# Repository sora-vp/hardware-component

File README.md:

<p align="center">
   
   <h1 align="center">SORA BUTTON MODULE</h1>
</p>

Ini adalah repositori pendukung [sora](https://github.com/reacto11mecha/sora) membuat tombol custom untuk memilih kandidat. Harapannya jika tidak ada perangkat touchscreen dan ada orang yang tidak bisa mengoperasikan komputer dengan baik masih bisa ikut memilih seperti biasanya.

## Cara pembuatan tombol custom

Di bawah ini saya akan menjelaskan bagaimana cara membuat modul tombol mandiri. Jika ada hal yang ingin dirubah, silahkan ubah sesuka hati sesuai bahan dan kreativitas masing-masing.

## Siapkan alat bahan

Pertama, siapkan terlebih dahulu alat dan bahan seperti

1. Gunting / cutter
2. Arduino Nano v3.0
3. Kardus bekas
4. Solder
5. Timah
6. Kabel (5 Meter, minimal 16 AWG)
7. Push button (8 buah)
8. Lem tembak beserta isinya.
9. PCB bolong (8x16cm)

> Catatan, untuk kardus dan arduino bisa menyesuaikan budget yang ada. Untuk tutorial di readme ini akan menggunakan kardus sebagai boxnya.

### 1. Buat kerangka

Hasil percobaan yang saya lakukan menghasilkan ukuran kerangka dengan bentuk jaring-jaring balok yang terlihat seperti ini.

Balok ini memiliki panjang 21 cm, lebar 15 cm, dan tinggi 7 cm.

### 2. Potong setiap bagian sebanyak dua lembar

Jika kerangka sudah dibuat, potong setiap bagian menjadi dua lembar kardus. Kemudian rekatkan menggunakan lem tembak supaya kekuatan kardus tidak terlalu lemah.

### 3. Mengatur jarak antar tombol

Untuk penempatan tombol, gunakan jaring-jaring balok dari kardus yang sudah dibuat menggunakan bagian tutup balok.

Panjang keseluruhan peletakan tombol itu 15cm untuk tombol kandidat dan aksi pilih dan pembatalan.

Untuk tombol angka yang nantinya digunakan untuk memilih kandidat, beri jarak 5cm dari atas juga 3 cm dari kanan dan kiri. Jarak antar tombol memiliki panjang 3.7cm supaya sesuai.

Tombol batal dan pilih juga beri jarak dari bawah. Tombol batal mengikuti posisi tombol nomor 1, sedangkan tombol pilih mengikuti posisi tombol nomor 5.

Tombol reload diposisikan sejajar dengan tombol nomor 5, posisi berjarak 3 cm dari kiri, 3.5 cm dari atas.

Jika sudah pasang lubangi titik-titik yang sudah dibuat, lalu pasang tombol yang sebelumnya sudah disiapkan. Kurang lebih hasilnya akan seperti ini.

> Jika memperhatikan gambar di atas ada 4 lubang di dua sisi kanan dan kiri kardus, itu berfungsi sebagai lubang udara. Ini opsional tetapi

### 4. Merancang sirkuit

Desain tombol ini sangat berdasar pada artikel [makeuseof.com](https://www.makeuseof.com/tag/make-custom-shortcut-buttons-arduino/) yang membahas cara membuat tombol sendiri. Kurang lebih gambar sirkuitnya sama, yang membedakan saya hanya menggunakan D2 sampai D9 saja.

Gambar di atas merupakan gambaran dasar sirkuitnya. Jika diperhatikan pin D2 sampai D9 menggunakan transistor 10k ohm yang warna emas terhubung ke pin arduino, sedangkan seluruh resisto warna coklat akan tersambung ke pin ground atau `GND`.

Gambar di atas adalah versi yang nantinya akan digunakan.

### 5. Menambahkan kabel ke tombol dan lem tombol

Jika sudah merancang sirkuitnya, sekarang sambungkan kabel ke tombol dengan cara menyolder kabel supaya sambungannya kuat. Berlaku untuk semua tombol, kira-kira tampaknya akan terlihat seperti dua gambar dibawah ini.

Jika sudah, lem semua tombol supaya tidak mudah lepas dari kardus. Hal ini juga dapat mengurangi kerusakan jika tombol ditekan terlalu keras.

### 6. Menyambungkan kabel ke sirkuit

Jika sudah menambahkan kabel ke tombol-tombol yang ada, saatnya menyambungkan tombol ke sirkuit yang sudah dibuat sebelumnya. `5V` terhubung ke satu sisi dari tombol, sisi yang lain akan terhubung ke digital pin dari arduino.

Jika berpatokan pada kode di bawah ini,

```ino
const int ESC_PIN = 4;
const int KEYBIND_1_PIN = 9;
const int KEYBIND_2_PIN = 8;
const int KEYBIND_3_PIN = 7;
const int KEYBIND_4_PIN = 6;
const int KEYBIND_5_PIN = 5;
const int ENTER_PIN = 3;
const int RELOAD_PIN = 2;
```

Maka

- Tombol 1 => Pin D9
- Tombol 2 => Pin D8
- Tombol 3 => Pin D7
- Tombol 4 => Pin D6
- Tombol 5 => Pin D5
- Tombol Escape (Kiri Bawah) => Pin D4
- Tombol Enter (Kanan Bawah) => Pin D3
- Tombol Reload (Sisi depan, bersamaan port usb) => Pin D2

Gambar setelah di sambungkan menggunakan solder akan terlihat seperti ini.

> Sekali lagi, sesuaikan dengan kebutuhan

### 7. Memposisikan sirkuit dengan papan reload

Pada tahap ini, posisikan pcb dengan arduino yang sudah di rekatkan dengan kardus yang memiliki tombol reload. Disarkankan posisi yang bisa dipasang port mini usb ke arduino berada berseberangan dengan tombol reload. Jika sudah, buat lubang kotak untuk tempat terhubungnya arduino melalui USB.

Tampak depan setelah dilubangi.

### 8. Lem semua komponen

Jika dirasa sudah beres, lem semua komponen yang akhirnya tampak seperti kotak yang memiliki tombol. Hasil akhirnya tampak seperti dibawah ini.

### 9. Finishing

Dibagian ini, silahkan di hias dan setiap tombol yang ada diberi keterangan supaya peserta pemilihan mengetahui fungsi dari setiap tombol.

## Upload sketch ke arduino

TODO: penjelasan

## Sumber Lain

- https://www.makeuseof.com/tag/make-custom-shortcut-buttons-arduino/

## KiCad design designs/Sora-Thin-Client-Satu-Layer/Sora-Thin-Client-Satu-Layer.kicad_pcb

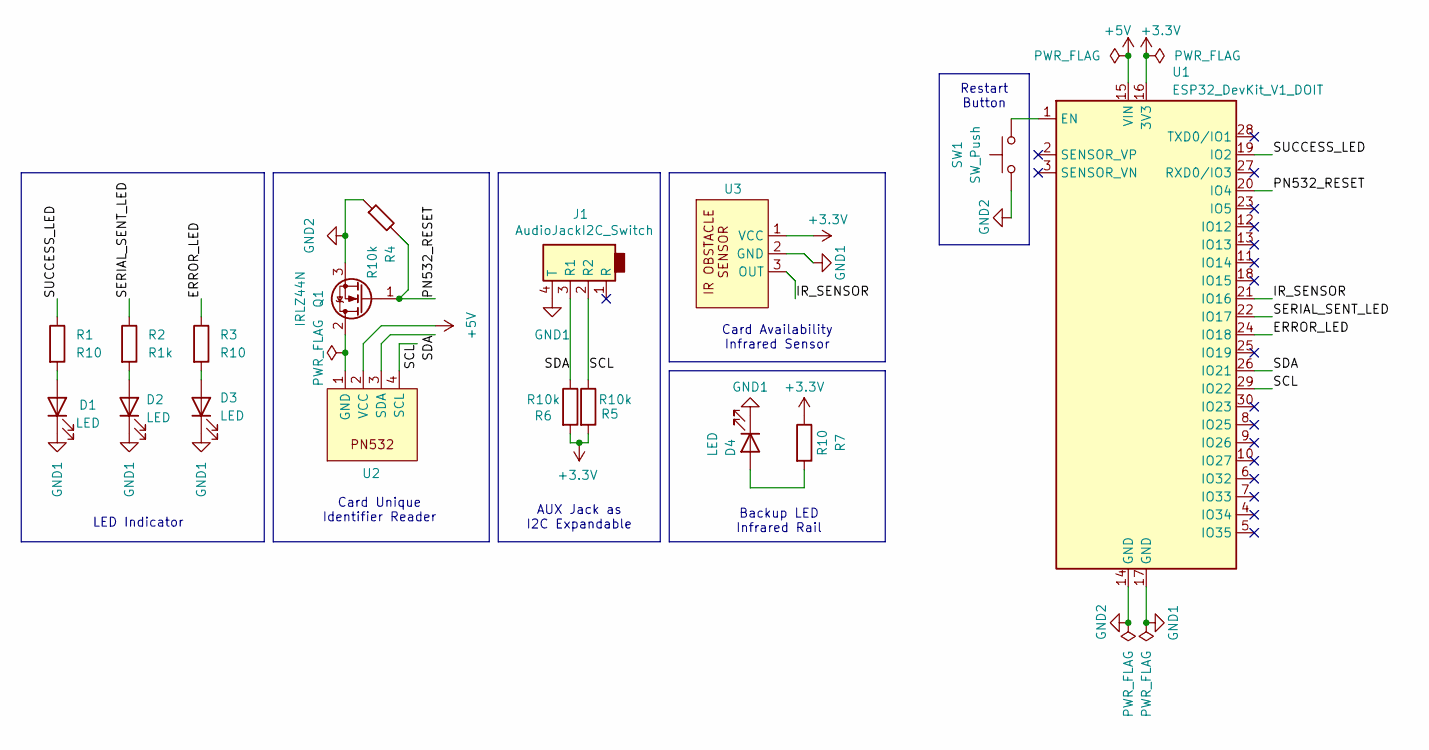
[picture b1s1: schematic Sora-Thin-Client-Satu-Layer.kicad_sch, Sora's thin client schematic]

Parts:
D1, D2, D3, D4: LED; PinHeader_1x02_P2.54mm_Vertical
J1: AudioJackI2C_Switch; PinHeader_1x04_P2.00mm_Vertical
Q1: IRLZ44N; TO-220-3_Vertical
R1, R3, R7: R10; R_Axial_DIN0204_L3.6mm_D1.6mm_P5.08mm_Horizontal
R2: R1k; R_Axial_DIN0204_L3.6mm_D1.6mm_P5.08mm_Horizontal
R4, R5, R6: R10k; R_Axial_DIN0204_L3.6mm_D1.6mm_P5.08mm_Horizontal
SW1: SW_Push; PinHeader_1x02_P2.54mm_Vertical
U1: ESP32_DevKit_V1_DOIT; esp32_devkit_v1_doit
U2: PinHeader_1x04_P2.54mm_Vertical
U3: PinHeader_1x03_P2.54mm_Vertical

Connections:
+3.3V: R5.2, R6.2, R7.1, U1.16 (3V3), U3.1 (VCC)
+5V: U1.15 (VIN), U2.2 (VCC)
/ERROR_LED: R3.1, U1.24 (IO18)
/IR_SENSOR: U1.21 (IO16), U3.3 (OUT)
/PN532_RESET: Q1.1 (G), R4.2, U1.20 (IO4)
/SCL: J1.2 (R2), R5.1, U1.29 (IO22), U2.4 (SCL)
/SDA: J1.3 (R1), R6.1, U1.26 (IO21), U2.3 (SDA)
/SERIAL_SENT_LED: R2.1, U1.22 (IO17)
/SUCCESS_LED: R1.1, U1.19 (IO2)
GND1: D1.1 (K), D2.1 (K), D3.1 (K), D4.1 (K), J1.4 (T), U1.17 (GND), U3.2 (GND)
GND2: Q1.3 (S), R4.1, SW1.1, U1.14 (GND)
unnamed: D1.2 (A), R1.2
unnamed: D2.2 (A), R2.2
unnamed: D3.2 (A), R3.2
unnamed: D4.2 (A), R7.2
unnamed: Q1.2 (D), U2.1 (GND)
unnamed: SW1.2, U1.1 (EN)

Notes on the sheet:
LED Indicator
AUX Jack as I2C Expandable
Restart Button
Backup LED Infrared Rail
Card Unique Identifier Reader
Card Availability Infrared Sensor

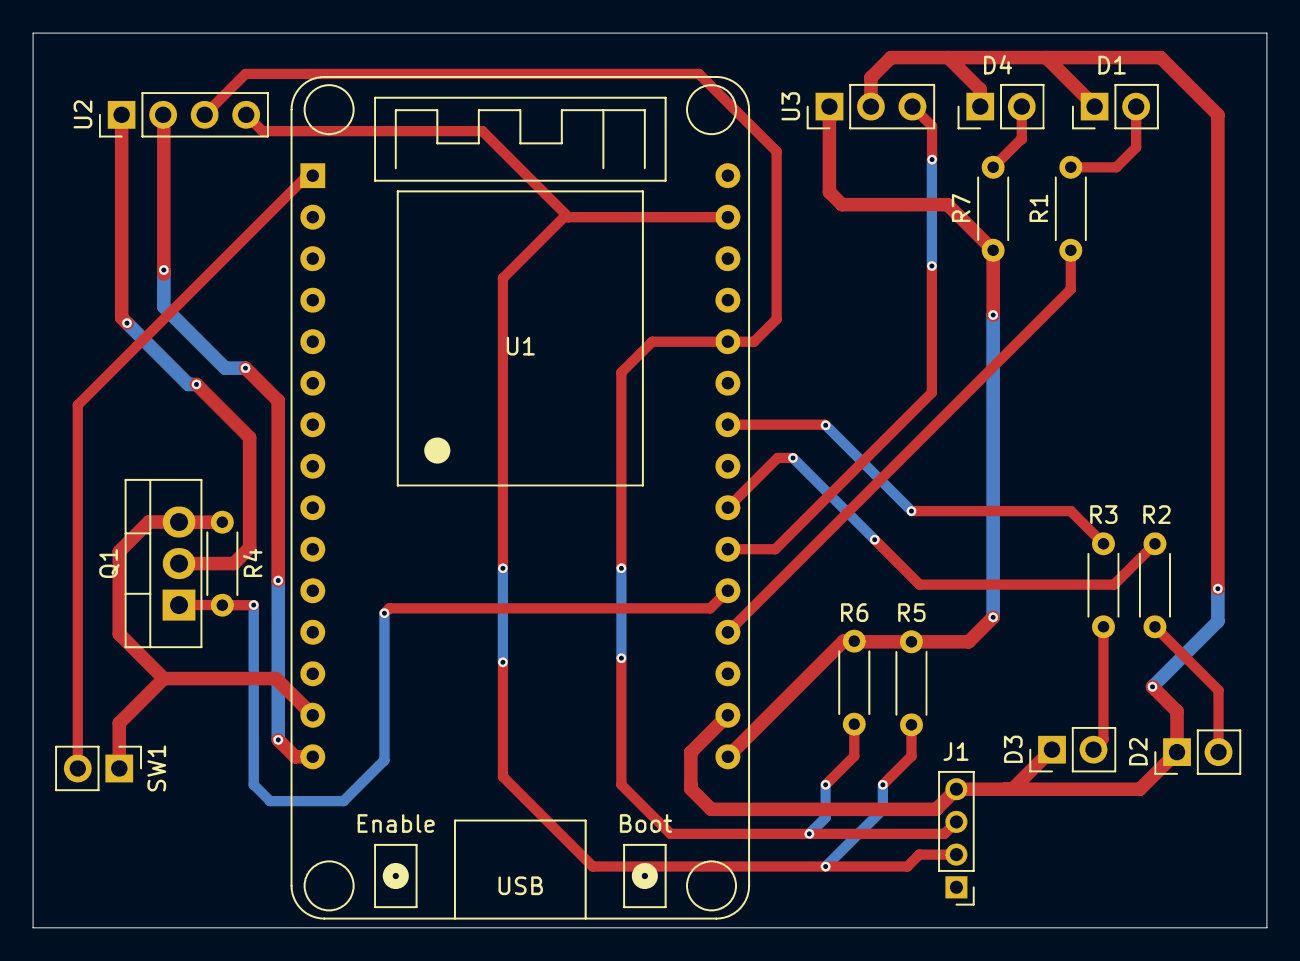
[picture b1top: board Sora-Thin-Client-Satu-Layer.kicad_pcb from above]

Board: 2 copper layers, 75.5 x 54.8 mm, 17 parts (0 on the bottom side), 17 nets.

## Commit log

2023-03-15 feat: initial commit
2023-03-15 feat: license
2023-03-16 feat: menambahkan pin dan action
2023-03-16 fix: mengubah waktu debounce
2023-03-16 fix: membuat respon lebih cepat
2023-03-16 chore: tetap menggunakan println
2023-03-20 feat: membuat tombol bekerja ketika keyup
2023-06-09 feat: menambahkan tutorial (WIP)
2023-08-18 feat: menggunakan desain yang baru
2023-08-19 docs: menambahkan penjelasan
2023-08-19 docs: memperbaiki typo gambar
2023-08-19 docs: menambahkan bagian pembuatan tombol
2023-08-19 docs: menambahkan gambar ke penjelasan yang rumpang
2024-07-07 fix: mengikuti perubahan nama repo
2024-07-07 feat: init websocket server
2024-07-08 feat: menambahkan fungsionalitas websocket
2024-07-08 feat: menambahkan ignore executable
2024-07-08 fix: memperbaiki bug windows yang harusnya di baca SORA malah ORA
2024-07-08 fix: tidak menggunakan mutex
2024-07-09 fix: pindah ke gorilla
2024-11-10 fix: implementasi start dan stop bit pada ws-server
2024-11-10 feat: menambahkan acknowledgement pada tombol
2024-12-17 feat: menambahkan thin client dan button mini
2024-12-18 fix: menggunakan vector untuk mengganti queue
2024-12-25 feat: menambahkan LED yang menjadi indikator pekerjaan mesin
2024-12-26 fix: memperbaiki bug I2C karena tidak refresh status koneksi ke PN532 dan format dokumen
2024-12-26 fix: memperbaiki bug gagal dalam copy buffer
2024-12-27 fix: menambahkan toleransi berapa lama vector pada button
    Saat first boot dan kartu belum di colok si thin client masih bisa komunikasi sama tombol, namun ketika kartu di lepas pasang pada timing dimana I2C bisa aja ga lanjut di baris 169 thin client, nah k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
2024-12-28 fix: menambahkan iterasi error supaya trigger mekanisme refresh koneksi
2024-12-28 feat: menambahkan task baru untuk UX yang lebih masuk akal
2025-01-02 feat: menambahkan skematik dan design pcb menggunakan kicad (2 Layer)
2025-01-02 fix: memperbaiki referensi yang rusak karena rename
2025-01-02 feat: menambahkan design pcb yang bisa di print manual
2025-01-02 fix: memperbaiki jalur dan tidak rotate design
2025-01-02 fix: lampu wajib horizontal
2025-01-03 fix: memperlebar ukuran supaya mudah pada saat solder
    bersama coach sam dkk
2025-01-04 fix: ws mah bukan firmware
